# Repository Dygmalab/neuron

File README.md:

# neuron
Neuron PCB of the Dygma Raise keyboard

Licensed under CERN-OHL and distributed as is without any additional warranty or documentation.

#### Usefull links
[Neuron](https://github.com/Dygmalab/neuron)

[Right side schematics](https://github.com/Dygmalab/raise-right-asym)

[Right bottom schematics](https://github.com/Dygmalab/right-lp)

[Left side schematics](https://github.com/Dygmalab/raise-left)

[Left bottom schematics](https://github.com/Dygmalab/left-lp)

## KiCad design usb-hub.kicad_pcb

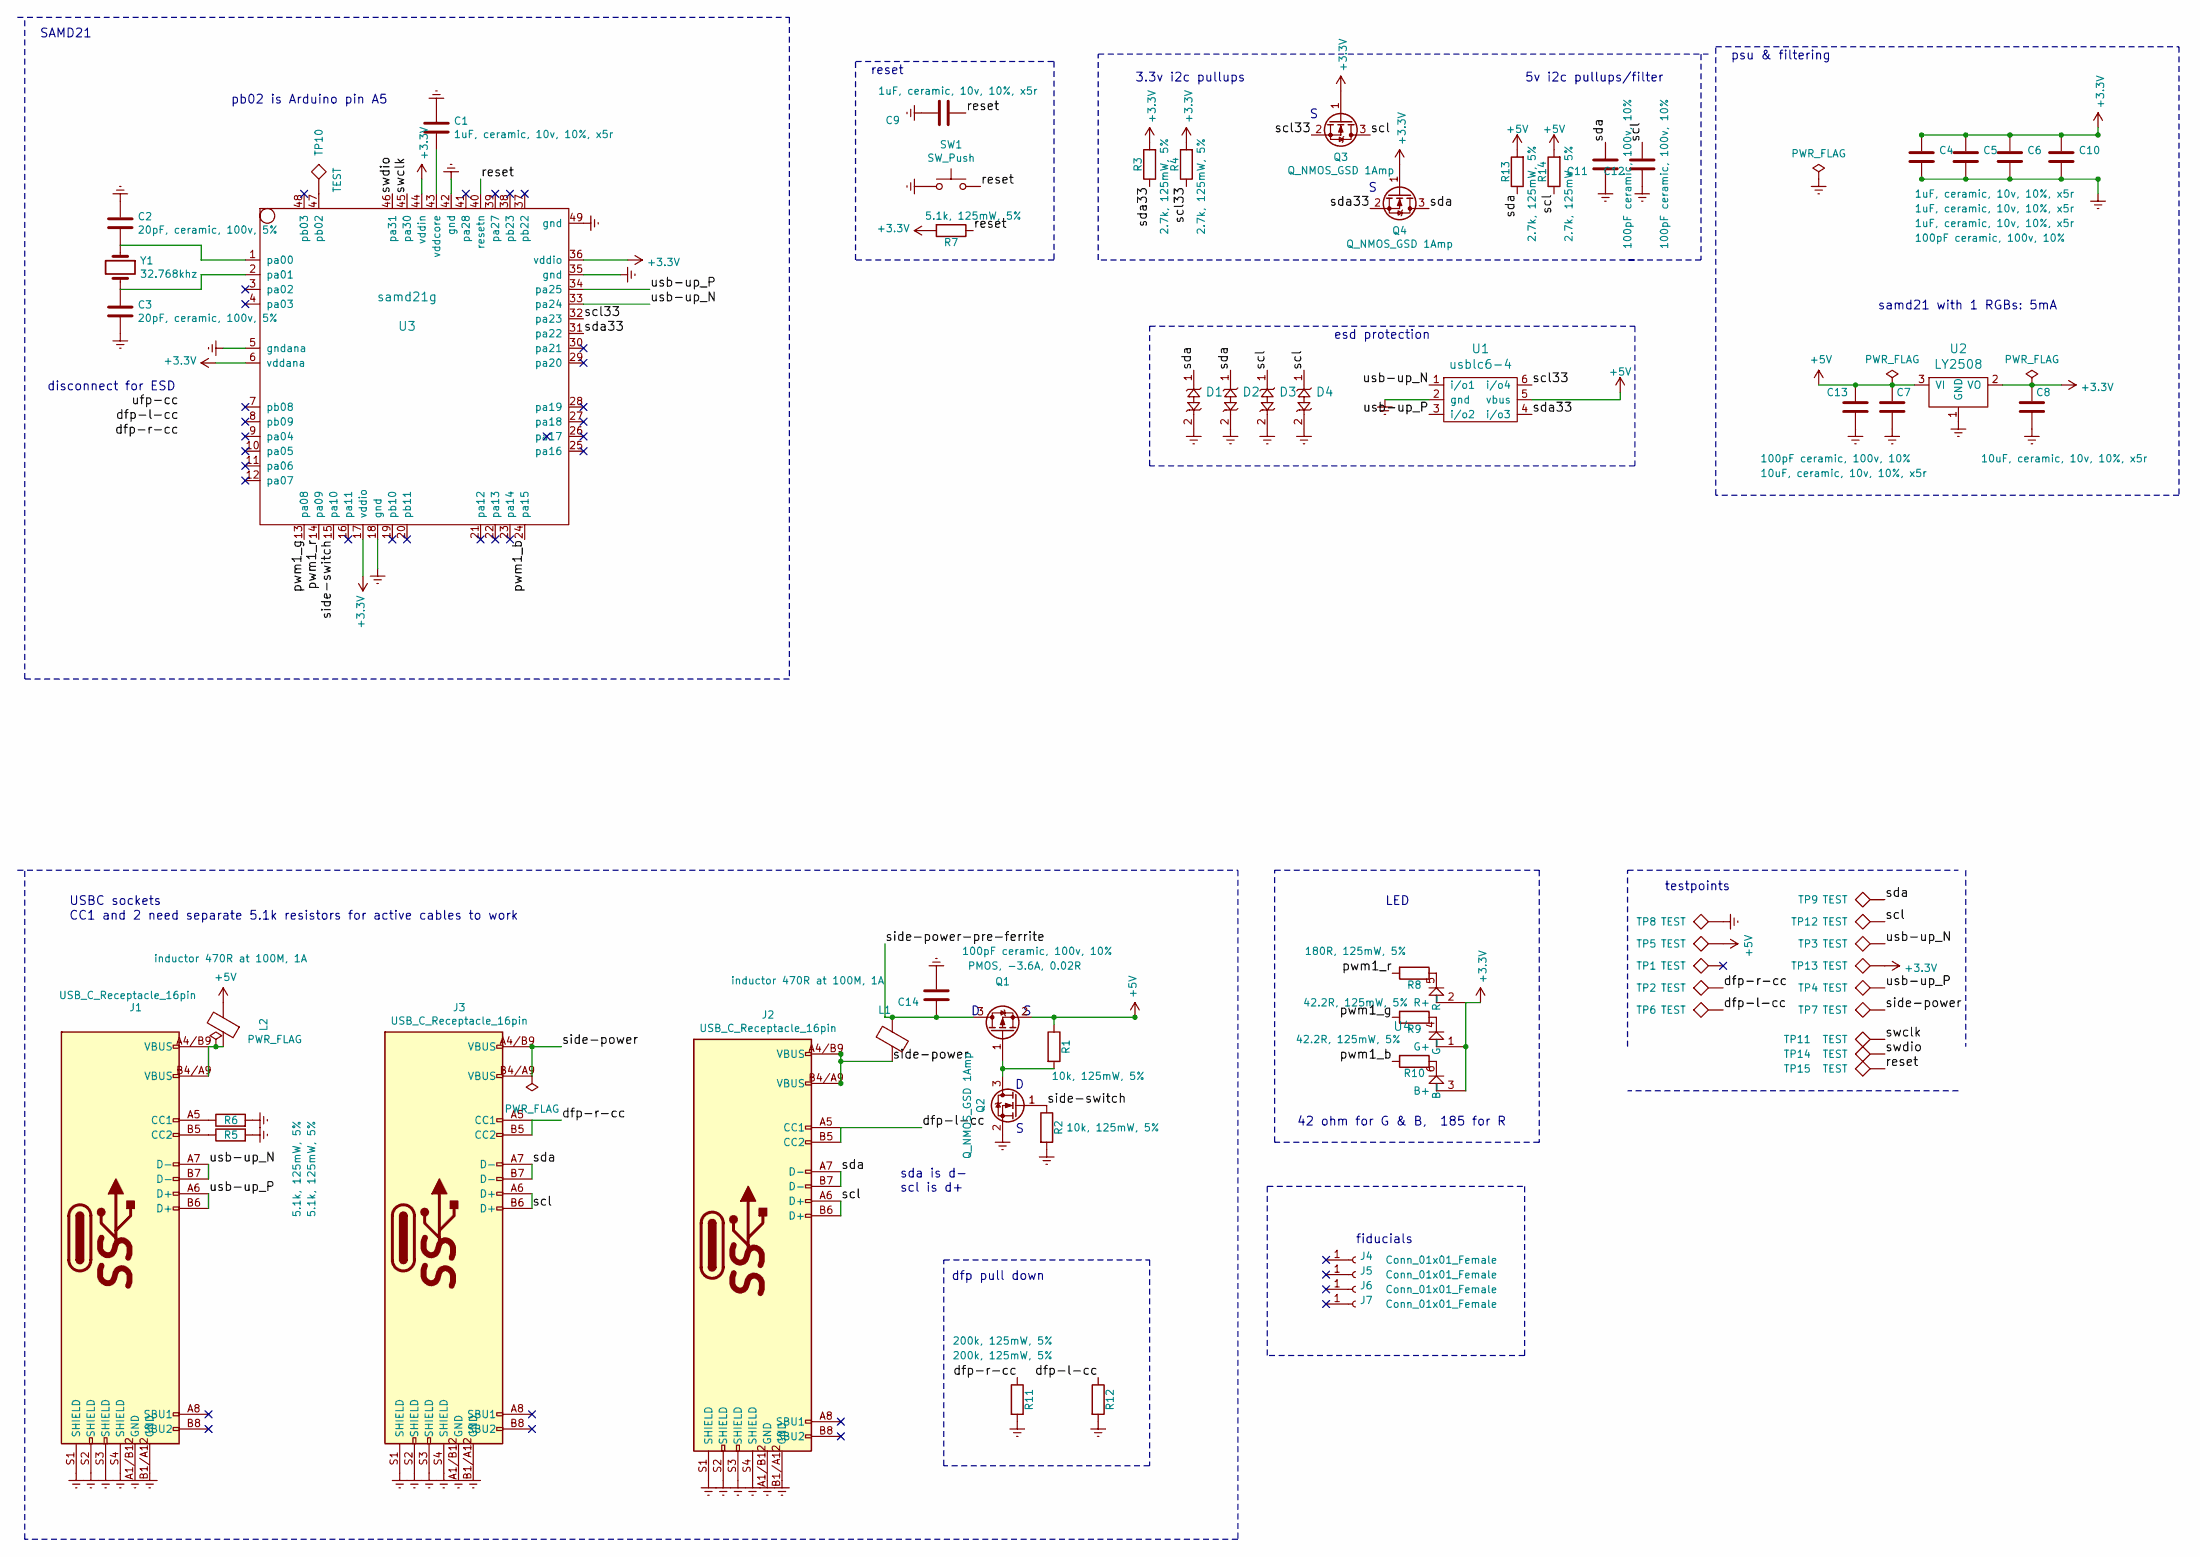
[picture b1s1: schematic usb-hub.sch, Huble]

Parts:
C1, C4, C5, C6: 1uF, ceramic, 10v, 10%, x5r; C_0603; farnell # 1865556
C2, C3: 20pF, ceramic, 100v, 5%; C_0603; farnell # 1865475
C7, C8: 10uF, ceramic, 10v, 10%, x5r; C_0603; farnell # 1288201
C9: 1uF, ceramic, 10v, 10%, x5r; C_0603; farnell # 2821263
C10, C11, C12, C13, C14: 100pF ceramic, 100v, 10%; C_0603; farnell # 2821263
D1, D2, D3, D4: ESD-diode; sod882
J1, J2, J3: USB_C_Receptacle_16pin; usb-c-16smt
J4, J5, J6, J7: Conn_01x01_Female; Fiducial_0.5mm_Dia_1mm_Outer
L1, L2: inductor 470R at 100M, 1A; R_0603; farnell # 1515745
Q1: PMOS, -3.6A, 0.02R; SOT-23; farnell # 2061419
Q2, Q3, Q4: Q_NMOS_GSD 1Amp; SOT-323_SC-70; farnell # 2061403
R1, R2: 10k, 125mW, 5%; R_0603; farnell # 2447230
R3, R4, R13, R14: 2.7k, 125mW, 5%; R_0603; farnell # 2447324
R5, R6: 5.1k, 125mW, 5%; R_0603; farnell # 2447404
R7: 5.1k, 125mW, 5%; R_0603; farnell # 2447230
R8: 180R, 125mW, 5%; R_0603; farnell # 2447267
R9, R10: 42.2R, 125mW, 5%; R_0603; farnell # 2694864
R11, R12: 200k, 125mW, 5%; R_0603; farnell # 2447291
SW1: SW_Push; reset-button
TP1, TP2, TP3, TP4, TP5, TP6, TP7, TP8, TP9, TP10, TP11, TP12, TP13, TP14, TP15: TEST; testpoint
U1: usblc6-4; SOT-23-6; farnell # 1295311
U2: LY2508; SOT-23; farnell # 2218573
U3: samd21g; QFN-48-1EP_7x7mm_Pitch0.5mm; farnell # 2409249
U4: 4 pin RGB led, com anode; 3528-4p
Y1: 32.768khz; Crystal_SMD_3215-2pin_3.2x1.5mm; farnell # 2449501

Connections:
+3V3: C4.1, C5.1, C6.1, C8.1, C10.1, Q3.1 (G), Q4.1 (G), R3.2, R4.2, R7.2, TP13.1, U2.2 (VO), U3.6 (vddana), U3.17 (vddio), U3.36 (vddio), U3.44 (vddin), U4.1 (G+), U4.2 (R+), U4.3 (B+)
+5V: C7.1, C13.1, L2.2, Q1.2 (S), R1.1, R13.2, R14.2, TP5.1, U1.5 (vbus), U2.3 (VI)
/dfp-l-cc: J2.A5 (CC1), J2.B5 (CC2), R12.1, TP6.1
/dfp-r-cc: J3.A5 (CC1), J3.B5 (CC2), R11.1, TP2.1
/pwm1_b: R10.2, U3.24 (pa15)
/pwm1_g: R9.2, U3.13 (pa08)
/pwm1_r: R8.2, U3.14 (pa09)
/reset: C9.1, R7.1, SW1.2, TP15.1, U3.40 (resetn)
/scl: C12.2, D3.1, D4.1, J2.A6 (D+), J2.B6 (D+), J3.A6 (D+), J3.B6 (D+), Q3.3 (D), R14.1, TP12.1
/scl33: Q3.2 (S), R4.1, U1.6 (i/o4), U3.32 (pa23)
/sda: C11.2, D1.1, D2.1, J2.A7 (D-), J2.B7 (D-), J3.A7 (D-), J3.B7 (D-), Q4.3 (D), R13.1, TP9.1
/sda33: Q4.2 (S), R3.1, U1.4 (i/o3), U3.31 (pa22)
/side-power: J2.A4/B9 (VBUS), J2.B4/A9 (VBUS), J3.A4/B9 (VBUS), J3.B4/A9 (VBUS), L1.2, TP7.1
/side-power-pre-ferrite: C14.1, L1.1, Q1.3 (D)
/side-switch: Q2.1 (G), R2.1, U3.15 (pa10)
/swclk: TP11.1, U3.45 (pa30)
/swdio: TP14.1, U3.46 (pa31)
/usb-up_N: J1.A7 (D-), J1.B7 (D-), TP3.1, U1.1 (i/o1), U3.33 (pa24)
/usb-up_P: J1.A6 (D+), J1.B6 (D+), TP4.1, U1.3 (i/o2), U3.34 (pa25)
Earth: C1.1, C2.1, C3.2, C4.2, C5.2, C6.2, C7.2, C8.2, C9.2, C10.2, C11.1, C12.1, C13.2, C14.2, D1.2, D2.2, D3.2, D4.2, J1.A1/B12 (GND), J1.B1/A12 (GND), J1.S1 (SHIELD), J1.S2 (SHIELD), J1.S3 (SHIELD), J1.S4 (SHIELD), J2.A1/B12 (GND), J2.B1/A12 (GND), J2.S1 (SHIELD), J2.S2 (SHIELD), J2.S3 (SHIELD), J2.S4 (SHIELD), J3.A1/B12 (GND), J3.B1/A12 (GND), J3.S1 (SHIELD), J3.S2 (SHIELD), J3.S3 (SHIELD), J3.S4 (SHIELD), Q2.2 (S), R2.2, R5.2, R6.2, R11.2, R12.2, SW1.1, TP8.1, U1.2 (gnd), U2.1 (GND), U3.5 (gndana), U3.18 (gnd), U3.35 (gnd), U3.42 (gnd), U3.49 (gnd)
unnamed: C1.2, U3.43 (vddcore)
unnamed: C2.2, U3.1 (pa00), Y1.1
unnamed: C3.1, U3.2 (pa01), Y1.2
unnamed: J1.A4/B9 (VBUS), J1.B4/A9 (VBUS), L2.1
unnamed: J1.A5 (CC1), R6.1
unnamed: J1.B5 (CC2), R5.1
unnamed: Q1.1 (G), Q2.3 (D), R1.2
unnamed: R8.1, U4.5 (R-)
unnamed: R9.1, U4.4 (G-)
unnamed: R10.1, U4.6 (B-)
unnamed: TP10.1, U3.47 (pb02)

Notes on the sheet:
samd21 with 1 RGBs: 5mA
testpoints
esd protection
42 ohm for G & B, 185 for R
sda is d- scl is d+
dfp pull down
fiducials
3.3v i2c pullups
pb02 is Arduino pin A5
5v i2c pullups/filter
psu & filtering
reset
USBC sockets
LED
SAMD21
disconnect for ESD
CC1 and 2 need separate 5.1k resistors for active cables to work

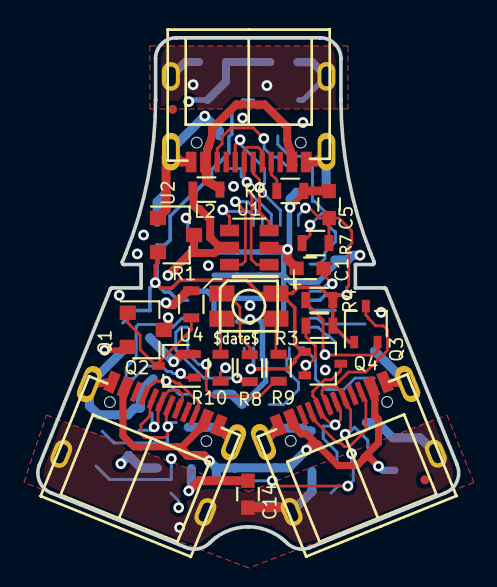
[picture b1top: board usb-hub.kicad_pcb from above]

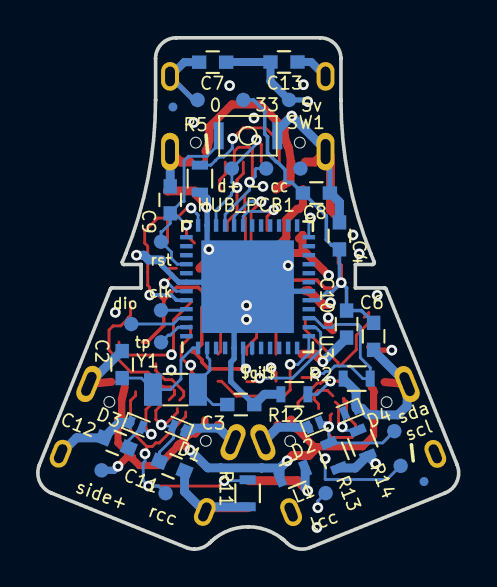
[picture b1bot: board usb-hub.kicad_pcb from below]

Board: 4 copper layers, 23.4 x 28.4 mm, 66 parts (42 on the bottom side), 31 nets.

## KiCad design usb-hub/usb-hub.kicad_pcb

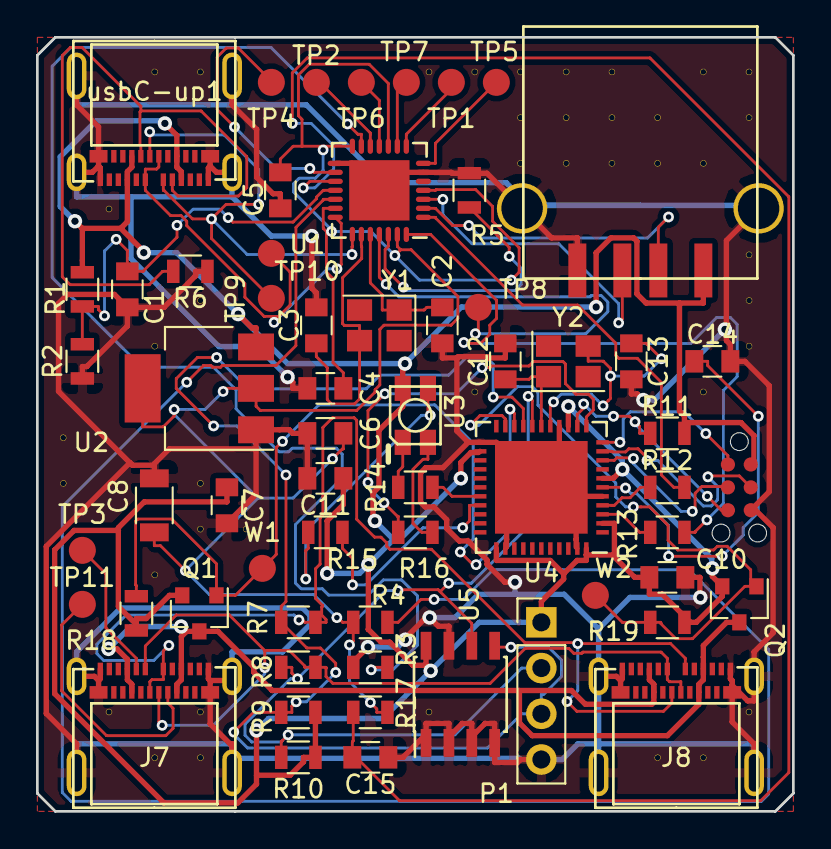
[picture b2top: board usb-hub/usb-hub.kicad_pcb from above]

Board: 2 copper layers, 42.0 x 43.0 mm, 102 parts (0 on the bottom side), 48 nets.

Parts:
C1, C14: 1u; C_0805
C2, C3, C12, C13: 20pf; C_0805
C4, C6, C7, C11, C15: 0.1u; C_0805
C5, C10: 4.7u; C_0805
C8: 47u; C_1206
J5: USB_A; usb-a-smt
J7, J8: USB_C_Receptacle; usb-c-24smt
P1: CONN_01X04; Pin_Header_Straight_1x04_Pitch2.54mm
P2: CONN_02X03; TC2030-MCP-NL
Q1, Q2: Q_PMOS_GSD; SOT-23
R1, R2, R3, R4, R11, R17, R18, R19: 10k; R_0805
R5: 12k; R_0805
R6: 5.1k; R_0805
R7, R8: 0R; R_0805
R9, R10: 4.7k; R_0805
R12, R13: 22r; R_0805
R14: 100R; R_0805
R15, R16: 60R; R_0805
TP1, TP2, TP3, TP4, TP5, TP6, TP7, TP8, TP9, TP10, TP11: TEST; Measurement_Point_Round-SMD-Pad_Small
U1: usb-2412; QFN-28-1EP_5x5mm_Pitch0.5mm
U2: LD1117S12TR_SOT223; SOT-223-3_TabPin2
U3: rgbled; 3528-4p
U4: ATmega32U4; QFN-44-1EP_7x7mm_Pitch0.5mm
U5: 24LC16; SOIC-8_3.9x4.9mm_Pitch1.27mm
V1_11, V1_12, V2_6, V2_17, V3_3, V3_9, V3_14, V3_18, V4_3, V4_8, V4_12, V4_13, V4_17, V4_18, V5_13, V9_3, V9_17, V10_3, V10_10, V11_3, V11_4, V11_5, V12_3, V12_4, V12_5, V13_3, V13_4, V13_5, V14_4, V14_5, V14_18, V15_3, V15_5, V15_10, V15_18, V16_3, V16_4, V16_7, V16_8, V16_9, V16_17: AUTO_VIA; VIA_MATRIX
W1, W2: TEST_1P; Measurement_Point_Round-SMD-Pad_Small
Y1, Y2: Crystal_GND24; Crystal_SMD_3225-4pin_3.2x2.5mm
usbC-up1: USB_C_Receptacle; usb-c-24smt

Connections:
+3V3: C4.1, C5.1, C6.1, C8.1, R4.1, R17.2, U1.4, U1.10, U1.14, U1.20, U1.27, U2.2
+5C: J7.A4, J7.A9, J7.B4, J7.B9, J8.A4, J8.A9, J8.B4, J8.B9, Q1.3, Q2.3
+5V: C7.1, C10.1, C11.1, J5.1, P1.1, P2.2, Q1.2, Q2.2, R1.2, R9.2, R10.2, R11.2, R18.2, R19.2, U2.3, U3.1, U4.2, U4.7, U4.14, U4.24, U4.34, U4.44, U5.8, usbC-up1.A4, usbC-up1.A9, usbC-up1.B4, usbC-up1.B9
/ext-usb-n: J5.2, U1.2
/ext-usb-p: J5.3, U1.3
/huble/left-switch: Q1.1, R18.1, U4.20, W1.1
/huble/miso: P2.1, U4.11
/huble/mosi: P2.4, U4.10
/huble/pwm_b: R16.2, U4.12
/huble/pwm_g: R15.2, U4.30
/huble/pwm_r: R14.2, U4.29
/huble/reset: P2.5, R11.1, U4.13
/huble/right-switch: Q2.1, R19.1, U4.21, W2.1
/huble/sck: P2.3, U4.9
/huble/scl: P1.2, R8.1, R10.1, U4.18, U5.6
/huble/sda: P1.3, R7.1, R9.1, U4.19, U5.5
/huble/usbc-dn: J7.A7, J7.B7, J8.A7, J8.B7, R7.2
/huble/usbc-dp: J7.A6, J7.B6, J8.A6, J8.B6, R8.2
/usb-up-n: TP10.1, U1.21, usbC-up1.A7, usbC-up1.B7
/usb-up-p: TP9.1, U1.22, usbC-up1.A6, usbC-up1.B6
Earth: C1.2, C2.1, C3.2, C4.2, C5.2, C6.2, C7.2, C8.2, C10.2, C11.2, C12.2, C13.2, C14.2, C15.2, J5.4, J5.5, J7.A1, J7.A12, J7.B1, J7.B12, J7.S1, J8.A1, J8.A12, J8.B1, J8.B12, J8.S1, P1.4, P2.6, R2.1, R3.1, R5.1, R6.2, U1.6, U1.15, U1.29, U2.1, U4.5, U4.15, U4.23, U4.35, U4.43, U4.45, U5.1, U5.2, U5.3, U5.4, U5.7, V1_11.1, V1_12.1, V2_6.1, V2_17.1, V3_3.1, V3_9.1, V3_14.1, V3_18.1, V4_3.1, V4_8.1, V4_12.1, V4_13.1, V4_17.1, V4_18.1, V5_13.1, V9_3.1, V9_17.1, V10_3.1, V10_10.1, V11_3.1, V11_4.1, V11_5.1, V12_3.1, V12_4.1, V12_5.1, V13_3.1, V13_4.1, V13_5.1, V14_4.1, V14_5.1, V14_18.1, V15_3.1, V15_5.1, V15_10.1, V15_18.1, V16_3.1, V16_4.1, V16_7.1, V16_8.1, V16_9.1, V16_17.1, usbC-up1.A1, usbC-up1.A12, usbC-up1.B1, usbC-up1.B12, usbC-up1.S1
unnamed: C1.1, R1.1, R2.2, U1.18
unnamed: C2.2, U1.24, Y1.1
unnamed: C3.1, U1.23, Y1.3
unnamed: C12.1, U4.17, Y2.1
unnamed: C13.1, U4.16, Y2.3
unnamed: C14.1, U4.6
unnamed: C15.1, R17.1, U1.17
unnamed: J7.A5, TP3.1
unnamed: J7.B5, TP11.1
unnamed: R3.2, U1.13
unnamed: R4.2, U1.19
unnamed: R5.2, U1.26
unnamed: R6.1, usbC-up1.A5, usbC-up1.B5
unnamed: R12.1, U4.4
unnamed: R13.1, U4.3
unnamed: R14.1, U3.5
unnamed: R15.1, U3.4
unnamed: R16.1, U3.6
unnamed: TP1.1, U1.8
unnamed: TP2.1, U1.12
unnamed: TP4.1, U1.16
unnamed: TP5.1, U1.7
unnamed: TP6.1, U1.11
unnamed: TP7.1, U1.9
unnamed: TP8.1, U1.25
atmega-usb-n: R13.2, U1.28
atmega-usb-p: R12.2, U1.1

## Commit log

2018-01-19 fixed usb routing, added reset, bigger board, dygma logo
2018-01-25 switched to smt usbc plugs and added power switching for both sockets
2018-01-25 fixed a track bug
2018-01-26 moved design files up 1 dir
2018-01-26 fixed missing cap on schematic, and fixed up post move netlist
2018-02-07 netlist
2018-02-09 remove wrong farnell codes, use same 47u tant cap in both places
2018-03-05 updated for BOM
2018-03-05 fixed wrong i2c pinout text
2018-03-09 contact technology 16pin USBC
2018-03-09 mid layout arm
2018-03-13 v2.1 ready for fab
2018-03-20 bom updated for 0603 parts and farnell order
2018-03-23 fixed vddcore error
2018-04-02 v2.2 - new hub chip, regulator and USB A
2018-04-02 fixed ref position
2018-04-09 farnell numberse
2018-04-09 added dimensions on the drawing layer
2018-04-13 fix some BOM values
2018-04-17 21g part
2018-04-17 changed micro, working on port switches
2018-04-18 differential routing, test pads
2018-04-18 4 esd diodes
2018-04-19 v2.3 sent to fab
2018-04-23 updated part numbers and specs
2018-05-21 remove wrong farnell partnum
2018-05-21 missing pro and config
2018-05-21 missing cache lib
2018-05-21 usb esd protection
2018-05-21 footprints in submodule
2018-05-25 removed hub and new board layout
2018-05-30 wip neuron layout
2018-06-22 routed
2018-06-27 added holes
2018-06-27 better ground pours
2018-06-29 ansi/iso bom
2018-06-29 sed script for fixing steps
2018-07-03 pcb colours
2018-07-06 regulator
2018-07-16 hide many values
2018-07-25 submodules
2018-07-25 fixes for gp
2018-08-06 led updated to show fp on fab layer
2018-08-28 submodule
2018-08-28 moved sockets in by 1.25mm
2018-09-03 moving sockets
2018-09-03 replaced programming header with test pads
2018-09-04 keep outs ok, silk screen done
2018-09-05 dnp esd and add inductor name to component value
2018-09-05 fixed broken testpoint positions
2018-09-06 logo path
2018-09-06 moved regulator out of keep out zone
2018-09-06 moved test points further away from board
2018-09-13 final checks
2018-09-20 fix mixup of swclk and swdio pads in schematic, updated changed inductor text to board file
2018-09-20 ignore
2018-10-12 add datasheet to esd protector
2018-11-15 100pf caps for ESD and I2C level shifter
2018-11-15 split git version into git and date
2018-11-28 changed visible layers, removed drawings
2018-12-13 slight change to USBC routing and changed USBC connectors mask around locator pins
2018-12-14 increased outline of edge cuts
2018-12-17 added big pads for USBC
2018-12-21 change usbC to smt type
2018-12-21 change usb ESD protector to be placed
2018-12-21 change fiducial to SMD type
2019-01-16 improve clarity of polarity of u5
2019-01-22 esd fixes: remove adc connections, protect usb +-, move esd protection
2019-01-22 thicker line for pin 1 of sot6
2019-02-07 remove tiny translator and go back to 2 mosfets, also fix farnell number on 2.7k R
2019-02-20 led partnum update
2019-02-27 move cap label
2019-04-02 thickened power traces
2019-04-02 few more gnd vias for the high speed tracks
2019-04-03 bom consolidation
2019-04-16 change submodules to github
2019-04-24 fixed reset filter
2019-05-27 ESD fixes recommmended by ASIM. Also better caps distribution
2019-06-10 added part number for ASIM ESD diode
2019-06-21 ESD diodes -> SMT
2019-07-08 fix missing USB CC resistor
2019-07-22 component refs moved
2019-07-22 fixed bsilk for new R
2019-12-19 fix led footprint
2020-03-23 update usb C socket partnum
